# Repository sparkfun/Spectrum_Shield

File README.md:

SparkFun Spectrum Shield
========================

[*SparkFun Spectrum Shield (DEV-13116)*](https://www.sparkfun.com/products/13116)

 This shield can be used to create sound visualizers, detect patterns in music or add sound activation to your microcontroller projects.

Repository Contents
-------------------
* **/Firmware** - Example Arduino Sketch
* **/Hardware** - All Eagle design files (.brd, .sch)
* **/Production** - Test bed files and production panel files

Documentation
--------------
* **[Hookup Guide](https://learn.sparkfun.com/tutorials/spectrum-shield-hookup-guide-v2)** - Basic hookup guide for the Spectrum Shield.
* **[SparkFun Fritzing repo](https://github.com/sparkfun/Fritzing_Parts)** - Fritzing diagrams for SparkFun products.
* **[SparkFun 3D Model repo](https://github.com/sparkfun/3D_Models)** - 3D models of SparkFun products. 

Product Versions
----------------
* [DEV-13116](https://www.sparkfun.com/products/13116) - Version 1.6
* [DEV-10306](https://www.sparkfun.com/products/10306) - Version 1.4. Retired. 

License Information
-------------------

This product is _**open source**_! 

Please review the LICENSE.md file for license information. 

If you have any questions or concerns on licensing, please contact technical support on our [SparkFun forums](https://forum.sparkfun.com/viewforum.php?f=152).

Distributed as-is; no warranty is given.

- Your friends at SparkFun.

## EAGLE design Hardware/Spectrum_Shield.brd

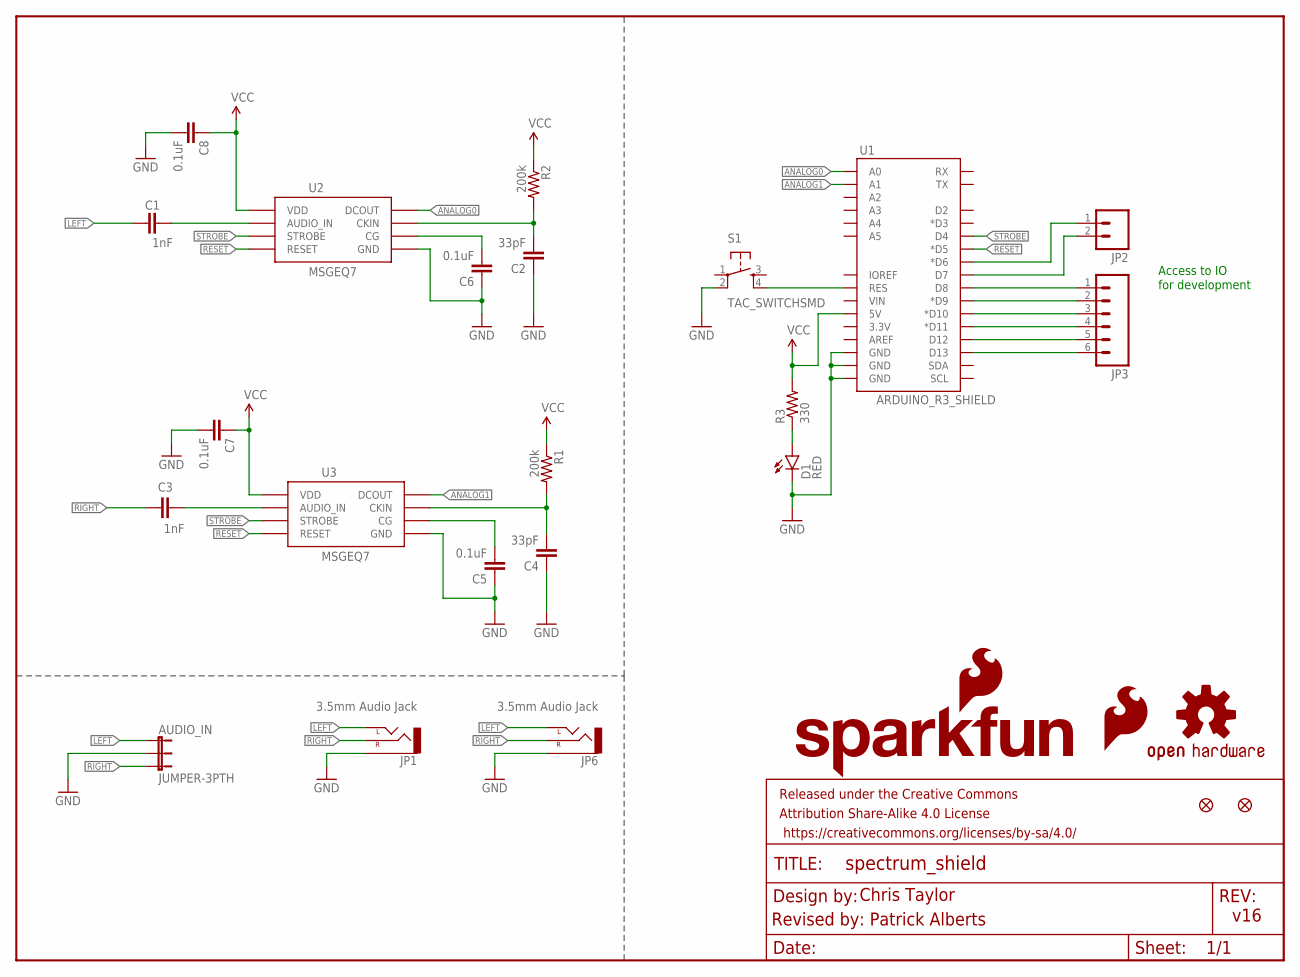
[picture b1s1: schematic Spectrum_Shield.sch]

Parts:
AUDIO_IN: JUMPER-3PTH; 1X03
C1, C3: 1nF; 0603-CAP
C2, C4: 33pF; 0603-CAP
C5, C6, C7, C8: 0.1uF; 0603-CAP
D1: RED; LED-0603
FRAME1: FRAME-LETTER; CREATIVE_COMMONS
JP1, JP6: 3.5mm Audio Jack; AUDIO-JACK-3.5MM-SMD
JP2: M02PTH; 1X02
JP3: M06SIP; 1X06
JP4, JP5: FIDUCIAL1X2; FIDUCIAL-1X2
LOGO1: OSHW-LOGOM; OSHW-LOGO-M
LOGO2: SFE_LOGO_FLAME.2_INCH; SFE_LOGO_FLAME_.2
LOGO3: SFE_LOGO_NAME_FLAME.1_INCH; SFE_LOGO_NAME_FLAME_.1
R1, R2: 200k; 0603-RES
R3: 330; 0603-RES
S1: TAC_SWITCHSMD; TACTILE-SWITCH-SMD
U1: ARDUINO_R3_SHIELD; UNO_R3_SHIELD
U2, U3: MSGEQ7SOIC; SOIC8

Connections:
ANALOG0: U1.A0, U2.3 (DCOUT)
ANALOG1: U1.A1, U3.3 (DCOUT)
GND: AUDIO_IN.2, C2.1, C4.1, C5.1, C6.1, C7.2, C8.2, D1.C, JP1.SLEEVE, JP6.SLEEVE, S1.2, U1.GND@0 (GND), U1.GND@1 (GND), U1.GND@2 (GND), U2.2 (GND), U3.2 (GND)
LEFT: AUDIO_IN.1, C1.1, JP1.TIP (LEFT), JP6.TIP (LEFT)
unnamed: C1.2, U2.5 (AUDIO_IN)
unnamed: C3.2, U3.5 (AUDIO_IN)
unnamed: C4.2, R1.2, U3.8 (CKIN)
unnamed: C2.2, R2.2, U2.8 (CKIN)
unnamed: C5.2, U3.6 (CG)
unnamed: C6.2, U2.6 (CG)
unnamed: D1.A, R3.1
unnamed: JP2.1, U1.D6 (*D6)
unnamed: JP2.2, U1.D7
unnamed: JP3.1, U1.D8
unnamed: JP3.2, U1.D9 (*D9)
unnamed: JP3.3, U1.D10 (*D10)
unnamed: JP3.4, U1.D11 (*D11)
unnamed: JP3.5, U1.D12
unnamed: JP3.6, U1.D13
unnamed: S1.4, U1.RES
RESET: U1.D5 (*D5), U2.7 (RESET), U3.7 (RESET)
RIGHT: AUDIO_IN.3, C3.1, JP1.RING (RIGHT), JP6.RING (RIGHT)
STROBE: U1.D4, U2.4 (STROBE), U3.4 (STROBE)
VCC: C7.1, C8.1, R1.1, R2.1, R3.2, U1.5V, U2.1 (VDD), U3.1 (VDD)

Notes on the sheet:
Access to IO
for development
v16
Chris Taylor
Revised by: Patrick Alberts

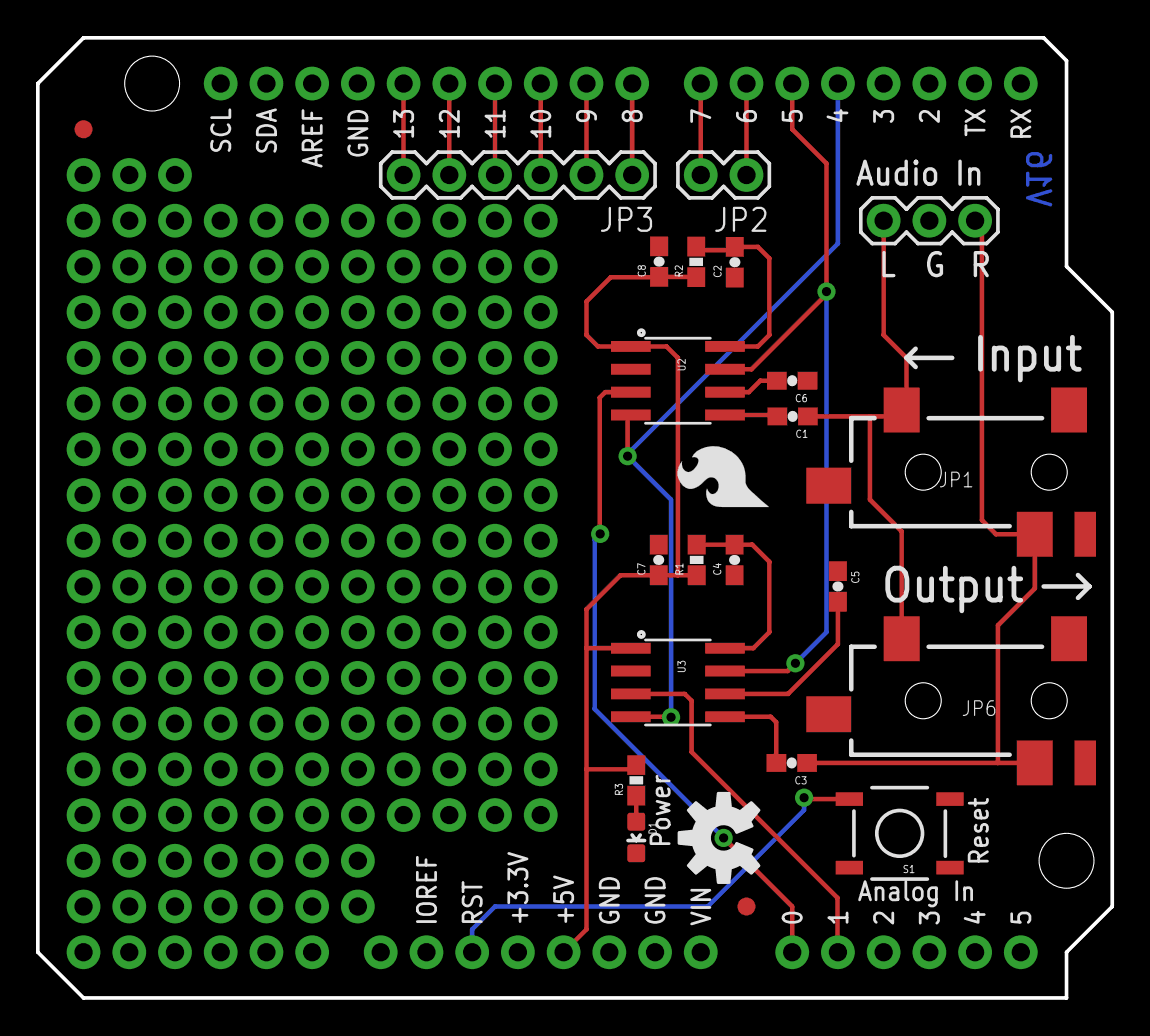
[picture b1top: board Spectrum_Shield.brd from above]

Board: 2 copper layers, 59.7 x 53.3 mm, 29 parts (1 on the bottom side), 24 nets.

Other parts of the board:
U$1, U$3: STAND-OFF-TIGHT

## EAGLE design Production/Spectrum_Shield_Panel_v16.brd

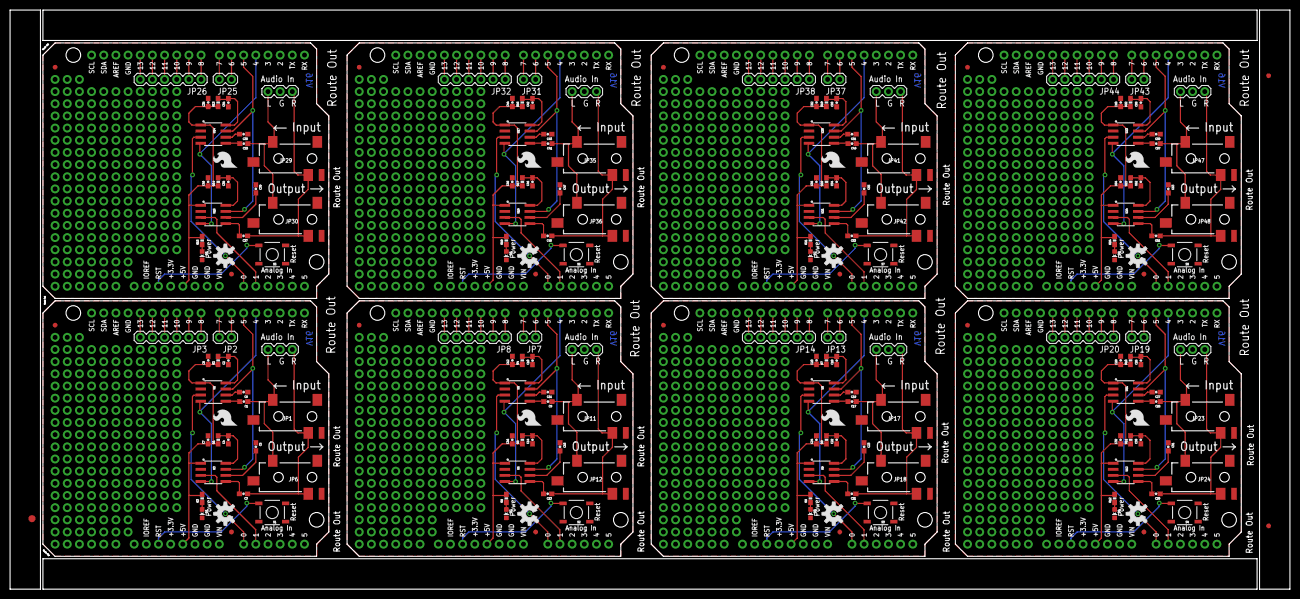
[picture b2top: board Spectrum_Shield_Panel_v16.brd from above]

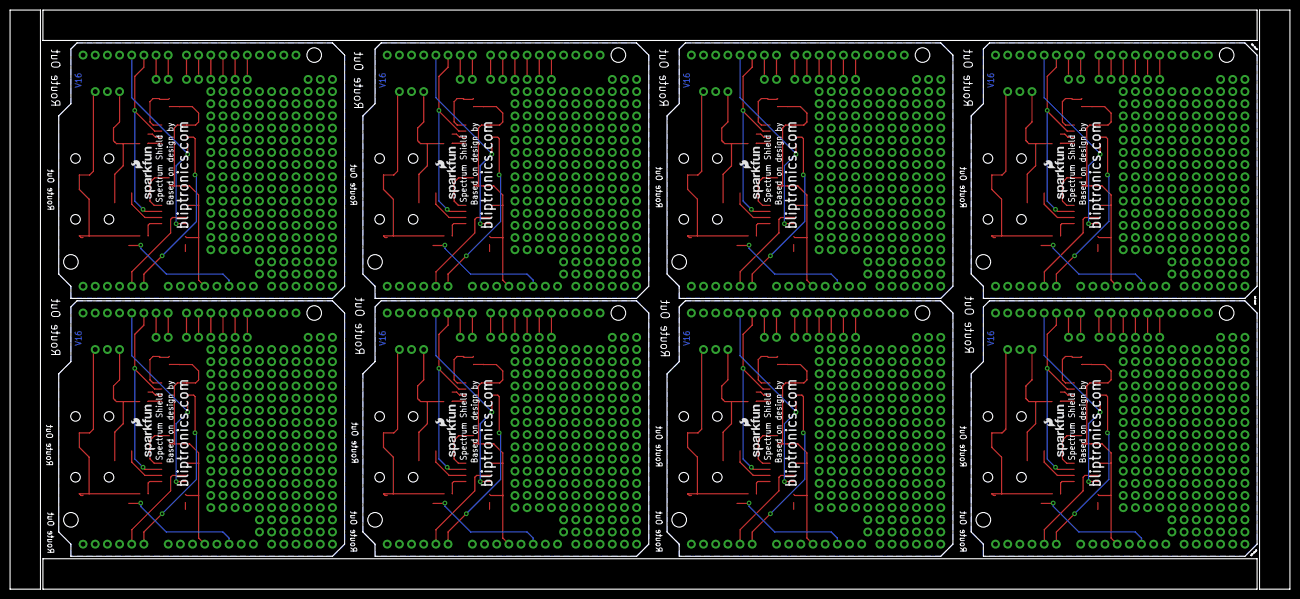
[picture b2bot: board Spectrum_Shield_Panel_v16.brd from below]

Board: 2 copper layers, 267.2 x 120.9 mm, 227 parts (8 on the bottom side), 192 nets.

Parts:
AUDIO_IN, AUDIO_IN1, AUDIO_IN2, AUDIO_IN3, AUDIO_IN4, AUDIO_IN5, AUDIO_IN6, AUDIO_IN7: JUMPER-3PTH; 1X03
C1, C3, C9, C13, C17, C21, C25, C29, C33, C37, C41, C45, C49, C53, C57, C61: 1nF; 0603-CAP
C2, C4, C10, C14, C18, C22, C26, C30, C34, C38, C42, C46, C50, C54, C58, C62: 33pF; 0603-CAP
C5, C6, C7, C8, C11, C12, C15, C16, C19, C20, C23, C24, C27, C28, C31, C32, C35, C36, C39, C40, C43, C44, C47, C48, C51, C52, C55, C56, C59, C60, C63, C64: 0.1uF; 0603-CAP
D1, D2, D3, D4, D5, D6, D7, D8: RED; LED-0603
E$1, E$2: FIDUCIAL-1X2
E$3: FIDUCIAL-1.5X3
JP1, JP6, JP11, JP12, JP17, JP18, JP23, JP24, JP29, JP30, JP35, JP36, JP41, JP42, JP47, JP48: 3.5mm Audio Jack; AUDIO-JACK-3.5MM-SMD
JP2, JP7, JP13, JP19, JP25, JP31, JP37, JP43: 1X02
JP3, JP8, JP14, JP20, JP26, JP32, JP38, JP44: 1X06
JP4, JP5, JP9, JP10, JP15, JP16, JP21, JP22, JP27, JP28, JP33, JP34, JP39, JP40, JP45, JP46: FIDUCIAL1X2; FIDUCIAL-1X2
LOGO1, LOGO4, LOGO7, LOGO10, LOGO13, LOGO16, LOGO19, LOGO22: OSHW-LOGOM; OSHW-LOGO-M
LOGO2, LOGO6, LOGO9, LOGO12, LOGO15, LOGO18, LOGO21, LOGO24: SFE_LOGO_FLAME.2_INCH; SFE_LOGO_FLAME_.2
LOGO3, LOGO5, LOGO8, LOGO11, LOGO14, LOGO17, LOGO20, LOGO23: SFE_LOGO_NAME_FLAME.1_INCH; SFE_LOGO_NAME_FLAME_.1
R1, R2, R4, R5, R7, R8, R10, R11, R13, R14, R16, R17, R19, R20, R22, R23: 200k; 0603-RES
R3, R6, R9, R12, R15, R18, R21, R24: 330; 0603-RES
S1, S2, S3, S4, S5, S6, S7, S8: TAC_SWITCHSMD; TACTILE-SWITCH-SMD
U1, U4, U7, U10, U13, U16, U19, U22: ARDUINO_R3_SHIELD; UNO_R3_SHIELD
U2, U3, U5, U6, U8, U9, U11, U12, U14, U15, U17, U18, U20, U21, U23, U24: MSGEQ7SOIC; SOIC8
U$1, U$2, U$3, U$4, U$5, U$6, U$7, U$8, U$9, U$10, U$11, U$12, U$13, U$14, U$15, U$16: STAND-OFF-TIGHT

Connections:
ANALOG0: U1.A0, U2.3
ANALOG1: U1.A1, U3.3
ANALOG2: U4.A0, U5.3
ANALOG3: U4.A1, U6.3
ANALOG4: U7.A0, U8.3
ANALOG5: U7.A1, U9.3
ANALOG6: U10.A0, U11.3
ANALOG7: U10.A1, U12.3
ANALOG8: U13.A0, U14.3
ANALOG9: U13.A1, U15.3
ANALOG10: U16.A0, U17.3
ANALOG11: U16.A1, U18.3
ANALOG12: U19.A0, U20.3
ANALOG13: U19.A1, U21.3
ANALOG14: U22.A0, U23.3
ANALOG15: U22.A1, U24.3
GND: AUDIO_IN.2, C2.1, C4.1, C5.1, C6.1, C7.2, C8.2, D1.C, JP1.SLEEVE, JP6.SLEEVE, S1.2, U1.GND@0, U1.GND@1, U1.GND@2, U2.2, U3.2
GND1: AUDIO_IN1.2, C10.1, C11.1, C12.2, C14.1, C15.1, C16.2, D2.C, JP11.SLEEVE, JP12.SLEEVE, S2.2, U4.GND@0, U4.GND@1, U4.GND@2, U5.2, U6.2
GND2: AUDIO_IN2.2, C18.1, C19.1, C20.2, C22.1, C23.1, C24.2, D3.C, JP17.SLEEVE, JP18.SLEEVE, S3.2, U7.GND@0, U7.GND@1, U7.GND@2, U8.2, U9.2
GND3: AUDIO_IN3.2, C26.1, C27.1, C28.2, C30.1, C31.1, C32.2, D4.C, JP23.SLEEVE, JP24.SLEEVE, S4.2, U10.GND@0, U10.GND@1, U10.GND@2, U11.2, U12.2
GND4: AUDIO_IN4.2, C34.1, C35.1, C36.2, C38.1, C39.1, C40.2, D5.C, JP29.SLEEVE, JP30.SLEEVE, S5.2, U13.GND@0, U13.GND@1, U13.GND@2, U14.2, U15.2
GND5: AUDIO_IN5.2, C42.1, C43.1, C44.2, C46.1, C47.1, C48.2, D6.C, JP35.SLEEVE, JP36.SLEEVE, S6.2, U16.GND@0, U16.GND@1, U16.GND@2, U17.2, U18.2
GND6: AUDIO_IN6.2, C50.1, C51.1, C52.2, C54.1, C55.1, C56.2, D7.C, JP41.SLEEVE, JP42.SLEEVE, S7.2, U19.GND@0, U19.GND@1, U19.GND@2, U20.2, U21.2
GND7: AUDIO_IN7.2, C58.1, C59.1, C60.2, C62.1, C63.1, C64.2, D8.C, JP47.SLEEVE, JP48.SLEEVE, S8.2, U22.GND@0, U22.GND@1, U22.GND@2, U23.2, U24.2
LEFT: AUDIO_IN.1, C1.1, JP1.TIP, JP6.TIP
LEFT1: AUDIO_IN1.1, C9.1, JP11.TIP, JP12.TIP
LEFT2: AUDIO_IN2.1, C17.1, JP17.TIP, JP18.TIP
LEFT3: AUDIO_IN3.1, C25.1, JP23.TIP, JP24.TIP
LEFT4: AUDIO_IN4.1, C33.1, JP29.TIP, JP30.TIP
LEFT5: AUDIO_IN5.1, C41.1, JP35.TIP, JP36.TIP
LEFT6: AUDIO_IN6.1, C49.1, JP41.TIP, JP42.TIP
LEFT7: AUDIO_IN7.1, C57.1, JP47.TIP, JP48.TIP
unnamed: C1.2, U2.5
unnamed: C3.2, U3.5
unnamed: C4.2, R1.2, U3.8
unnamed: C2.2, R2.2, U2.8
unnamed: C5.2, U3.6
unnamed: C6.2, U2.6
unnamed: D1.A, R3.1
unnamed: JP2.1, U1.D6
unnamed: JP2.2, U1.D7
unnamed: JP3.1, U1.D8
unnamed: JP3.2, U1.D9
unnamed: JP3.3, U1.D10
unnamed: JP3.4, U1.D11
unnamed: JP3.5, U1.D12
unnamed: JP3.6, U1.D13
unnamed: C9.2, U5.5
unnamed: C10.2, R4.2, U5.8
unnamed: C11.2, U5.6
unnamed: C13.2, U6.5
unnamed: C14.2, R5.2, U6.8
unnamed: C15.2, U6.6
unnamed: D2.A, R6.1
unnamed: JP7.2, U4.D7
unnamed: JP8.1, U4.D8
unnamed: JP8.2, U4.D9
unnamed: JP8.3, U4.D10
unnamed: JP8.4, U4.D11
unnamed: JP8.5, U4.D12
unnamed: JP8.6, U4.D13
unnamed: S1.4, U1.RES
unnamed: S2.4, U4.RES
unnamed: JP7.1, U4.D6
unnamed: C17.2, U8.5
unnamed: C18.2, R7.2, U8.8
unnamed: C19.2, U8.6
unnamed: C21.2, U9.5
unnamed: C22.2, R8.2, U9.8
unnamed: C23.2, U9.6
unnamed: D3.A, R9.1
unnamed: JP13.2, U7.D7
unnamed: JP14.1, U7.D8
unnamed: JP14.2, U7.D9
unnamed: JP14.3, U7.D10
unnamed: JP14.4, U7.D11
unnamed: JP14.5, U7.D12
unnamed: JP14.6, U7.D13
unnamed: S3.4, U7.RES
unnamed: JP13.1, U7.D6
unnamed: C25.2, U11.5
unnamed: C26.2, R10.2, U11.8
unnamed: C27.2, U11.6
unnamed: C29.2, U12.5
unnamed: C30.2, R11.2, U12.8
unnamed: C31.2, U12.6
unnamed: D4.A, R12.1
unnamed: JP19.2, U10.D7
unnamed: JP20.1, U10.D8
unnamed: JP20.2, U10.D9
unnamed: JP20.3, U10.D10
unnamed: JP20.4, U10.D11
unnamed: JP20.5, U10.D12
unnamed: JP20.6, U10.D13
unnamed: S4.4, U10.RES
unnamed: JP19.1, U10.D6
unnamed: C33.2, U14.5
unnamed: C34.2, R13.2, U14.8
unnamed: C35.2, U14.6
unnamed: C37.2, U15.5
unnamed: C38.2, R14.2, U15.8
unnamed: C39.2, U15.6
unnamed: D5.A, R15.1
unnamed: JP25.2, U13.D7
unnamed: JP26.1, U13.D8
unnamed: JP26.2, U13.D9
unnamed: JP26.3, U13.D10
unnamed: JP26.4, U13.D11
unnamed: JP26.5, U13.D12
unnamed: JP26.6, U13.D13
unnamed: S5.4, U13.RES
unnamed: JP25.1, U13.D6
unnamed: C41.2, U17.5
unnamed: C42.2, R16.2, U17.8
unnamed: C43.2, U17.6
unnamed: C45.2, U18.5
unnamed: C46.2, R17.2, U18.8
unnamed: C47.2, U18.6
unnamed: D6.A, R18.1
unnamed: JP31.2, U16.D7
unnamed: JP32.1, U16.D8
unnamed: JP32.2, U16.D9
unnamed: JP32.3, U16.D10
unnamed: JP32.4, U16.D11
unnamed: JP32.5, U16.D12
unnamed: JP32.6, U16.D13
unnamed: S6.4, U16.RES
unnamed: JP31.1, U16.D6
unnamed: C49.2, U20.5
unnamed: C50.2, R19.2, U20.8
unnamed: C51.2, U20.6
unnamed: C53.2, U21.5
unnamed: C54.2, R20.2, U21.8
unnamed: C55.2, U21.6
unnamed: D7.A, R21.1
unnamed: JP37.2, U19.D7
unnamed: JP38.1, U19.D8
unnamed: JP38.2, U19.D9
unnamed: JP38.3, U19.D10
unnamed: JP38.4, U19.D11
unnamed: JP38.5, U19.D12
unnamed: JP38.6, U19.D13
unnamed: S7.4, U19.RES
unnamed: JP37.1, U19.D6
unnamed: C57.2, U23.5
unnamed: C58.2, R22.2, U23.8
unnamed: C59.2, U23.6
unnamed: C61.2, U24.5
unnamed: C62.2, R23.2, U24.8
unnamed: C63.2, U24.6
unnamed: D8.A, R24.1
unnamed: JP43.2, U22.D7
unnamed: JP44.1, U22.D8
unnamed: JP44.2, U22.D9
unnamed: JP44.3, U22.D10
unnamed: JP44.4, U22.D11
unnamed: JP44.5, U22.D12
unnamed: JP44.6, U22.D13
unnamed: S8.4, U22.RES
unnamed: JP43.1, U22.D6
RESET: U1.D5, U2.7, U3.7
RESET1: U4.D5, U5.7, U6.7
RESET2: U7.D5, U8.7, U9.7
RESET3: U10.D5, U11.7, U12.7
RESET4: U13.D5, U14.7, U15.7
RESET5: U16.D5, U17.7, U18.7
RESET6: U19.D5, U20.7, U21.7
RESET7: U22.D5, U23.7, U24.7
RIGHT: AUDIO_IN.3, C3.1, JP1.RING, JP6.RING
RIGHT1: AUDIO_IN1.3, C13.1, JP11.RING, JP12.RING
RIGHT2: AUDIO_IN2.3, C21.1, JP17.RING, JP18.RING
RIGHT3: AUDIO_IN3.3, C29.1, JP23.RING, JP24.RING
RIGHT4: AUDIO_IN4.3, C37.1, JP29.RING, JP30.RING
RIGHT5: AUDIO_IN5.3, C45.1, JP35.RING, JP36.RING
RIGHT6: AUDIO_IN6.3, C53.1, JP41.RING, JP42.RING
RIGHT7: AUDIO_IN7.3, C61.1, JP47.RING, JP48.RING
STROBE: U1.D4, U2.4, U3.4
STROBE1: U4.D4, U5.4, U6.4
STROBE2: U7.D4, U8.4, U9.4
STROBE3: U10.D4, U11.4, U12.4
STROBE4: U13.D4, U14.4, U15.4
STROBE5: U16.D4, U17.4, U18.4
STROBE6: U19.D4, U20.4, U21.4
STROBE7: U22.D4, U23.4, U24.4
VCC: C7.1, C8.1, R1.1, R2.1, R3.2, U1.5V, U2.1, U3.1
VCC1: C12.1, C16.1, R4.1, R5.1, R6.2, U4.5V, U5.1, U6.1
VCC2: C20.1, C24.1, R7.1, R8.1, R9.2, U7.5V, U8.1, U9.1
VCC3: C28.1, C32.1, R10.1, R11.1, R12.2, U10.5V, U11.1, U12.1
VCC4: C36.1, C40.1, R13.1, R14.1, R15.2, U13.5V, U14.1, U15.1
VCC5: C44.1, C48.1, R16.1, R17.1, R18.2, U16.5V, U17.1, U18.1
VCC6: C52.1, C56.1, R19.1, R20.1, R21.2, U19.5V, U20.1, U21.1
VCC7: C60.1, C64.1, R22.1, R23.1, R24.2, U22.5V, U23.1, U24.1

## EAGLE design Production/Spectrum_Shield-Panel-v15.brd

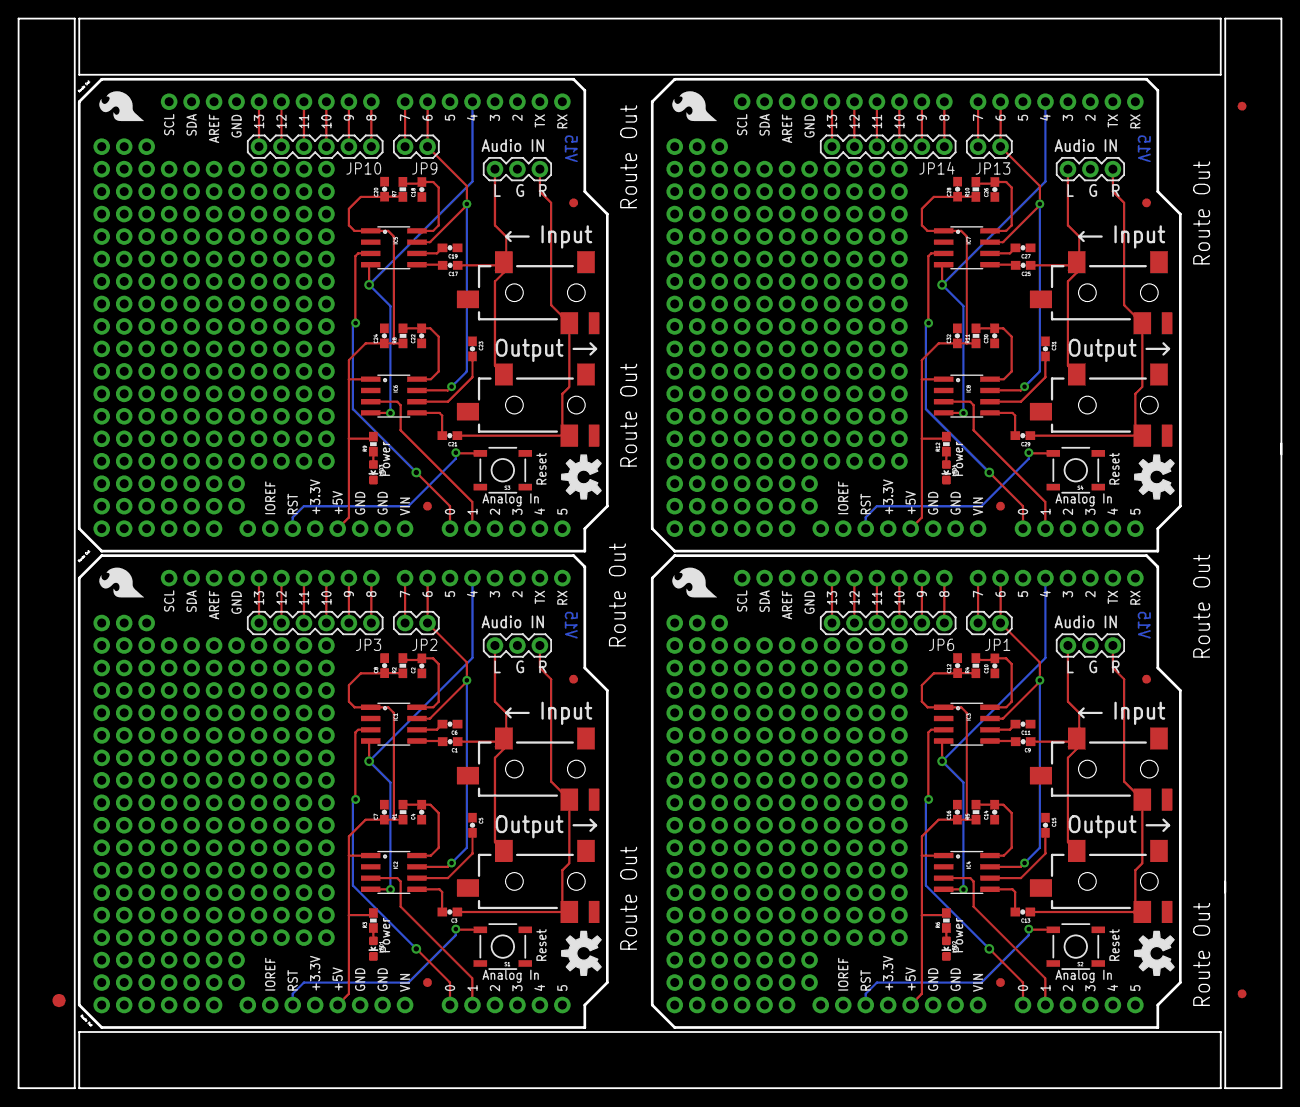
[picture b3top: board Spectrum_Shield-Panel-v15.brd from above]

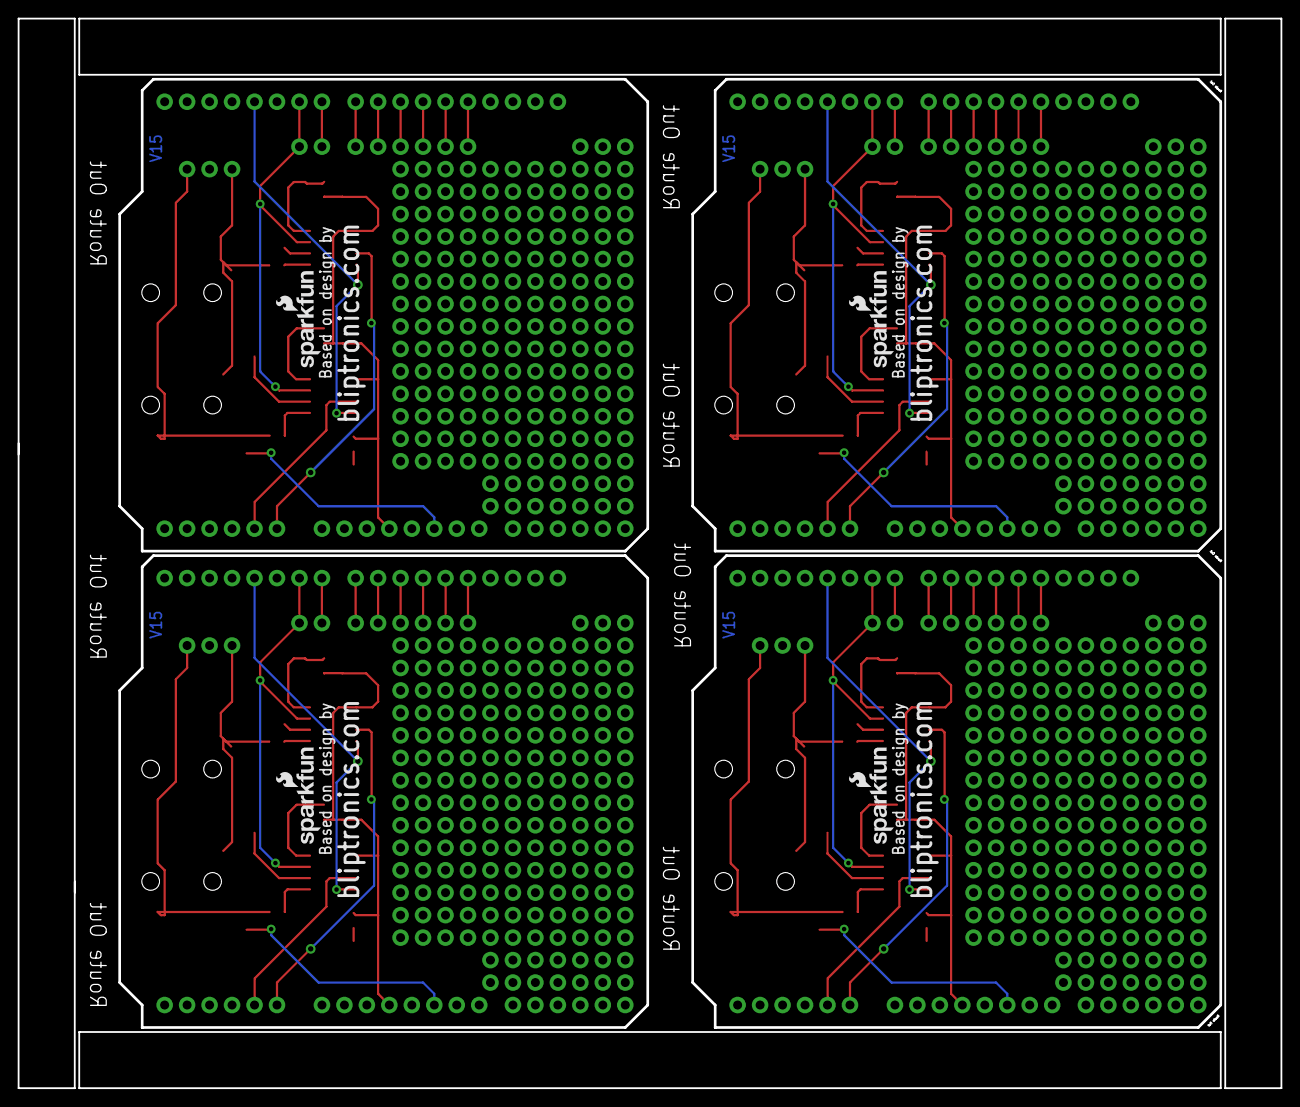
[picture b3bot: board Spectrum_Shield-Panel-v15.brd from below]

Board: 2 copper layers, 142.6 x 120.8 mm, 107 parts (4 on the bottom side), 92 nets.

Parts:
AUDIOJACK1, AUDIOJACK2, AUDIOJACK3, AUDIOJACK4, AUDIOJACK5, AUDIOJACK6, AUDIOJACK7, AUDIOJACK8: AUDIO-JACK-3.5MM-SMD
AUDIO_IN, AUDIO_IN1, AUDIO_IN2, AUDIO_IN3: JUMPER-3PTH; 1X03
C1, C3, C9, C13, C17, C21, C25, C29: 1000pF; 0603-CAP
C2, C4, C10, C14, C18, C22, C26, C30: 33pF; 0603-CAP
C5, C6, C7, C8, C11, C12, C15, C16, C19, C20, C23, C24, C27, C28, C31, C32: 0.1uF; 0603-CAP
E$1: FIDUCIAL-1.5X3
E$4, E$5: FIDUCIAL-1X2
IC1, IC2, IC3, IC4, IC5, IC6, IC7, IC8: MSGEQ7SOIC; SOIC8
JP1, JP2, JP9, JP13: 1X02
JP3, JP6, JP10, JP14: 1X06
JP4, JP5, JP7, JP8, JP11, JP12, JP15, JP16: FIDUCIAL1X2; FIDUCIAL-1X2
LED1, LED2, LED3, LED4: RED; LED-0603
LOGO1, LOGO4, LOGO7, LOGO10: OSHW-LOGOM; OSHW-LOGO-M
LOGO2, LOGO5, LOGO8, LOGO11: SFE_LOGO_FLAME.2_INCH; SFE_LOGO_FLAME_.2
LOGO3, LOGO6, LOGO9, LOGO12: SFE_LOGO_NAME_FLAME.1_INCH; SFE_LOGO_NAME_FLAME_.1
R1, R2, R4, R5, R7, R8, R10, R11: 200k; 0603-RES
R3, R6, R9, R12: 330; 0603-RES
S1, S2, S3, S4: TACTILE_SWITCH_SMD
U1, U2, U3, U4: ARDUINO_R3_SHIELD; UNO_R3_SHIELD

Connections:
ANALOG0: IC1.3, U1.A0
ANALOG1: IC2.3, U1.A1
ANALOG2: IC3.3, U2.A0
ANALOG3: IC4.3, U2.A1
ANALOG4: IC5.3, U3.A0
ANALOG5: IC6.3, U3.A1
ANALOG6: IC7.3, U4.A0
ANALOG7: IC8.3, U4.A1
GND: AUDIOJACK2.SLEEVE, AUDIO_IN.2, C2.1, C4.1, C5.1, C6.1, C7.2, C8.2, IC1.2, IC2.2, LED1.C, S1.2, U1.GND@0, U1.GND@1, U1.GND@2
GND1: AUDIOJACK4.SLEEVE, AUDIO_IN1.2, C10.1, C11.1, C12.2, C14.1, C15.1, C16.2, IC3.2, IC4.2, LED2.C, S2.2, U2.GND@0, U2.GND@1, U2.GND@2
GND2: AUDIOJACK6.SLEEVE, AUDIO_IN2.2, C18.1, C19.1, C20.2, C22.1, C23.1, C24.2, IC5.2, IC6.2, LED3.C, S3.2, U3.GND@0, U3.GND@1, U3.GND@2
GND3: AUDIOJACK8.SLEEVE, AUDIO_IN3.2, C26.1, C27.1, C28.2, C30.1, C31.1, C32.2, IC7.2, IC8.2, LED4.C, S4.2, U4.GND@0, U4.GND@1, U4.GND@2
LEFT: AUDIOJACK1.TIP, AUDIOJACK2.TIP, AUDIO_IN.1, C1.1
LEFT1: AUDIOJACK3.TIP, AUDIOJACK4.TIP, AUDIO_IN1.1, C9.1
LEFT2: AUDIOJACK5.TIP, AUDIOJACK6.TIP, AUDIO_IN2.1, C17.1
LEFT3: AUDIOJACK7.TIP, AUDIOJACK8.TIP, AUDIO_IN3.1, C25.1
unnamed: C1.2, IC1.5
unnamed: C3.2, IC2.5
unnamed: C4.2, IC2.8, R1.2
unnamed: C2.2, IC1.8, R2.2
unnamed: C5.2, IC2.6
unnamed: C6.2, IC1.6
unnamed: LED1.A, R3.1
unnamed: C9.2, IC3.5
unnamed: JP2.2, U1.D7
unnamed: JP3.1, U1.D8
unnamed: JP3.2, U1.D9
unnamed: JP3.3, U1.D10
unnamed: JP3.4, U1.D11
unnamed: JP3.5, U1.D12
unnamed: JP3.6, U1.D13
unnamed: C10.2, IC3.8, R4.2
unnamed: C11.2, IC3.6
unnamed: C13.2, IC4.5
unnamed: C14.2, IC4.8, R5.2
unnamed: C15.2, IC4.6
unnamed: LED2.A, R6.1
unnamed: JP1.2, U2.D7
unnamed: JP6.1, U2.D8
unnamed: JP6.2, U2.D9
unnamed: JP6.3, U2.D10
unnamed: JP6.4, U2.D11
unnamed: JP6.5, U2.D12
unnamed: JP6.6, U2.D13
unnamed: S1.4, U1.RES
unnamed: S2.4, U2.RES
unnamed: C17.2, IC5.5
unnamed: C18.2, IC5.8, R7.2
unnamed: C19.2, IC5.6
unnamed: C21.2, IC6.5
unnamed: C22.2, IC6.8, R8.2
unnamed: C23.2, IC6.6
unnamed: LED3.A, R9.1
unnamed: JP9.2, U3.D7
unnamed: JP10.1, U3.D8
unnamed: JP10.2, U3.D9
unnamed: JP10.3, U3.D10
unnamed: JP10.4, U3.D11
unnamed: JP10.5, U3.D12
unnamed: JP10.6, U3.D13
unnamed: S3.4, U3.RES
unnamed: C25.2, IC7.5
unnamed: C26.2, IC7.8, R10.2
unnamed: C27.2, IC7.6
unnamed: C29.2, IC8.5
unnamed: C30.2, IC8.8, R11.2
unnamed: C31.2, IC8.6
unnamed: LED4.A, R12.1
unnamed: JP13.2, U4.D7
unnamed: JP14.1, U4.D8
unnamed: JP14.2, U4.D9
unnamed: JP14.3, U4.D10
unnamed: JP14.4, U4.D11
unnamed: JP14.5, U4.D12
unnamed: JP14.6, U4.D13
unnamed: S4.4, U4.RES
RESET: IC1.7, IC2.7, JP2.1, U1.D6
RESET1: IC3.7, IC4.7, JP1.1, U2.D6
RESET2: IC5.7, IC6.7, JP9.1, U3.D6
RESET3: IC7.7, IC8.7, JP13.1, U4.D6
RIGHT: AUDIOJACK1.RING, AUDIOJACK2.RING, AUDIO_IN.3, C3.1
RIGHT1: AUDIOJACK3.RING, AUDIOJACK4.RING, AUDIO_IN1.3, C13.1
RIGHT2: AUDIOJACK5.RING, AUDIOJACK6.RING, AUDIO_IN2.3, C21.1
RIGHT3: AUDIOJACK7.RING, AUDIOJACK8.RING, AUDIO_IN3.3, C29.1
STROBE: IC1.4, IC2.4, U1.D4
STROBE1: IC3.4, IC4.4, U2.D4
STROBE2: IC5.4, IC6.4, U3.D4
STROBE3: IC7.4, IC8.4, U4.D4
VCC: C7.1, C8.1, IC1.1, IC2.1, R1.1, R2.1, R3.2, U1.5V
VCC1: C12.1, C16.1, IC3.1, IC4.1, R4.1, R5.1, R6.2, U2.5V
VCC2: C20.1, C24.1, IC5.1, IC6.1, R7.1, R8.1, R9.2, U3.5V
VCC3: C28.1, C32.1, IC7.1, IC8.1, R10.1, R11.1, R12.2, U4.5V

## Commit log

2014-07-16 int commit
2014-07-18 Computer Change
2014-07-21 computer change #2
2014-07-22 Upd audiojk/0603/ trace re-routes
    Updated the audio jack to smd, changed res/caps to 0603 as well as the
    LED. Added the OSHW logo and updated the shield to the R3.
2014-07-22 Trace Clean up.
2014-08-18 Fixed Sch, Added Input/Output Silk
2014-09-30 changed silk
2014-10-10 moved fiducials
2014-10-10 created panel v15
2014-11-11 Fixing a few flags on schematic
2015-01-19 Updating README to new product links, adding example sketch
2015-01-19 Adding old part URL
2015-02-24 Adding in demo sketches, fixing Production directory name
2015-02-24 Removing zip files
2015-05-12 Fixed Ground Issue
2015-05-12 QC checklist updated, fixed gnd / pin issue
2015-05-12 Fixed acid traps
2015-05-13 Fixed silk.
2015-05-22 Added stand offs, fixed silk. QC list / attributes
2015-05-28 Fixed QC Checklist Items
    1) Currently there are two 4-way junctions: both below each MSGEQ7
    symbol, each 4-way needs to split up into two 3-way junctions.
    (2) On the R3 symbol the VCC net crosses over the RESET net. It would be
    nice to reorganize these nets to eliminate the intersection all
    together.
    (3) The Audio jacks are currently named Audiojack1 and 2, these should
2015-07-07 deleted old panel, created new v16 panel
2015-12-14 Fixing pin declarations in code examples
2015-12-14 updating readme, adding license file
2020-01-29 Update
    Add minimum delay for strobe pulse width and for data to output
2020-01-31 Create SparkFun_Spectrum_Serial_Plotter_Demo.ino
    Create new, simpler plot example.
2020-02-05 Update Notation

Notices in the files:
parts and their libraries:
SparkFun-Capacitors: Licensing: Creative Commons ShareAlike 4.0 International - https://creativecommons.org/licenses/by-sa/4.0
SparkFun-Aesthetics: Released under the Creative Commons Attribution Share-Alike 4.0 License
SparkFun-Aesthetics: https://creativecommons.org/licenses/by-sa/4.0
